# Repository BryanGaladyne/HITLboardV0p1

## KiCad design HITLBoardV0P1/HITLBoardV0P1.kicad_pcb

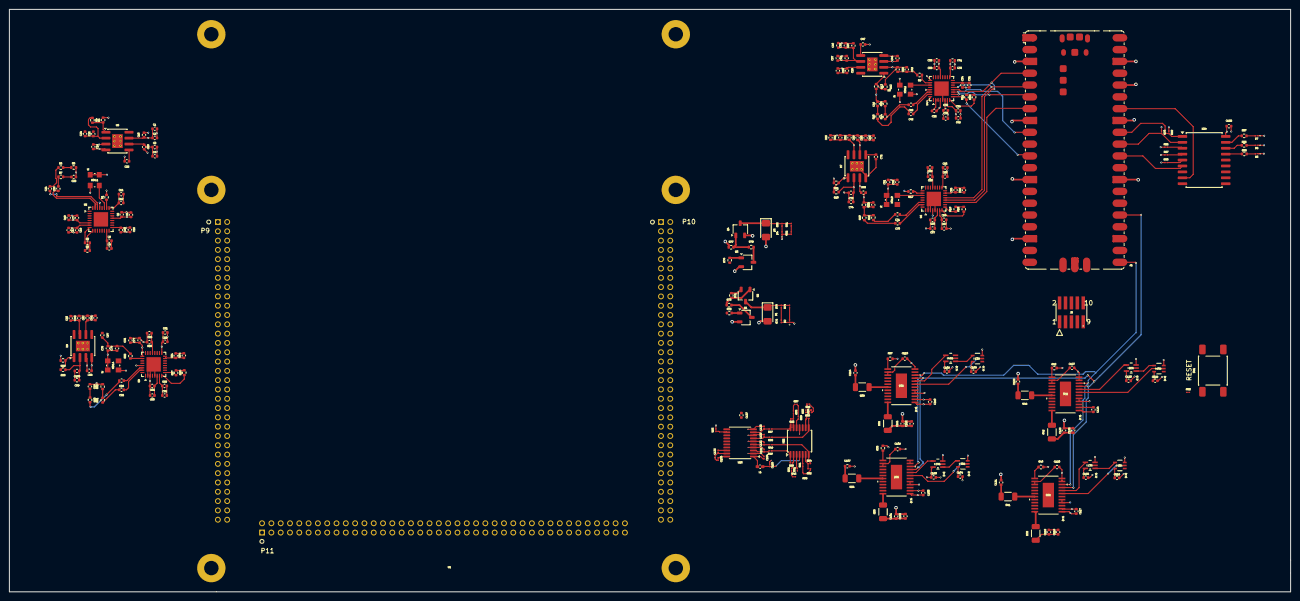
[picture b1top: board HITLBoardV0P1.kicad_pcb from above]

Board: 8 copper layers, 275.4 x 125.2 mm, 267 parts (0 on the bottom side), 160 nets.

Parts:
A1: RaspberryPi_Pico; RaspberryPi_Pico_SMD
C1, C2, C3, C4, C26, C27, C28, C29, C51, C52, C53, C54, C76, C77, C78, C79: 10u; C_0402_1005Metric
C5, C6, C7, C13, C14, C30, C31, C32, C38, C39, C55, C56, C57, C63, C64, C80, C81, C82, C88, C89: 10n; C_0402_1005Metric
C8, C9, C10, C16, C17, C20, C21, C23, C33, C34, C35, C41, C42, C45, C46, C48, C58, C59, C60, C66, C67, C70, C71, C73, C83, C84, C85, C91, C92, C95, C96, C98: .1U; C_0402_1005Metric
C11, C12, C15, C18, C19, C22, C25, C36, C37, C40, C43, C44, C47, C50, C61, C62, C65, C68, C69, C72, C75, C86, C87, C90, C93, C94, C97, C100: 1u; C_0402_1005Metric
C24, C49, C74, C99: 100n; C_0402_1005Metric
C101, C111, C118, C125: 100p; C_0402_1005Metric
C102, C103, C104, C105, C106, C107, C108, C109, C110, C112, C113, C114, C115, C116, C117, C119, C120, C121, C122, C123, C124, C126, C127, C128, C137, C138: 0.1u; C_0402_1005Metric
C129, C131, C132, C133, C134, C136: 0.1u; C_01005_0402Metric
C130, C135: 0.1U; C_01005_0402Metric
D1, D3: D_Schottky; D_1206_3216Metric_Pad1.42x1.75mm_HandSolder
D2, D4, D5, D6, D7: LED; LED_01005_0402Metric
J2: FTSH-105-01-L-DV; CON10_2X5_DU_FTSH_SAI
L1: L_Ferrite; L_0402_1005Metric_Pad0.77x0.64mm_HandSolder
Q1, Q3: NPN; TSOT-23_KSC1623GMTF
Q2, Q4: PMOS; TSOT-23_ZXMP6A14FQ
R1, R9, R17, R25: 12.4K; R_0402_1005Metric
R2, R3, R10, R11, R18, R19, R26, R27, R71, R77: 10K; R_0402_1005Metric
R4, R12, R20, R28: 2.94K; R_0402_1005Metric
R5, R13, R21, R29: 1.13K; R_0402_1005Metric
R6, R7, R14, R15, R22, R23, R30, R31: 49.9K; R_0402_1005Metric
R8, R16, R24, R32: 100K; R_0402_1005Metric
R33, R36, R39, R42: 10; R_1206_3216Metric
R34, R38, R41, R44: 15; R_1206_3216Metric
R35, R37, R40, R43: 15K; R_0402_1005Metric
R45, R46, R57, R58: 150; R_01005_0402Metric
R47, R48, R49, R50, R74, R80: 500; R_01005_0402Metric
R51, R52, R53, R54, R56, R59, R60, R61, R62, R63, R64: 100K; R_01005_0402Metric
R55: 1K; R_01005_0402Metric
R65, R66, R67, R68, R69, R70, R75, R81, R83: 10K; R_01005_0402Metric
R72, R78: 33; R_0402_1005Metric
R73, R79: 4.7K; R_0402_1005Metric
R76, R82: 3500; R_01005_0402Metric
R85, R86, R87: 75; R_0402_1005Metric
SW1: SW_Push; SW_Push_1P1T_NO_E-Switch_TL3301NxxxxxG
U1: TMDX570LC43HDK_Connectors; TMDX570LC43HDK
U2, U4, U6, U8: LAN8650B1-E/LMX; QFN-32-1EP_5x5mm_P0.5mm_EP3.1x3.1mm
U3, U5, U7, U9: LP38852MRX-ADJ/NOPB; SOIC-8-1EP_3.9x4.9mm_P1.27mm_EP2.29x3mm_ThermalVias
U10, U15, U18, U21: DAC7750IPWPR; PWP24_TEX
U11, U13, U16, U19: NC7SZ04P5X; SC-88A-5_1P35X2P2_ONS
U12, U14, U17, U20: SN74LVC1G08DCKR; DCK5
U22: TLV4387PWR; TSSOP-14_4.4x5mm_P0.65mm
U23: ADS131M04QPWRQ1; TSSOP-20_4.4x6.5mm_P0.65mm
U24: MCP23008-E/SO; SOIC-18W_7.5x11.6mm_P1.27mm
XTAL1, XTAL2, XTAL3, XTAL4: ECS-2520S33-250-FN-TR; ECS-2520S_ECS

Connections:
+3.3VP: A1.36 (3V3), C103.1, C104.1, C105.1, C108.1, C109.1, C110.1, C115.1, C116.1, C117.1, C122.1, C123.1, C124.1, C138.1, J2.1, R69.1, R70.1, R83.1, U10.2 (DVDD), U11.5 (VCC), U12.5 (VCC), U13.5 (VCC), U14.5 (VCC), U15.2 (DVDD), U16.5 (VCC), U17.5 (VCC), U18.2 (DVDD), U19.5 (VCC), U20.5 (VCC), U21.2 (DVDD), U24.18 (VDD)
+3V3: C1.1, C2.1, C3.1, C4.1, C11.1, C12.1, C13.1, C14.1, C15.1, C16.1, C17.1, C18.1, C26.1, C27.1, C28.1, C29.1, C36.1, C37.1, C38.1, C39.1, C40.1, C41.1, C42.1, C43.1, C51.1, C52.1, C53.1, C54.1, C61.1, C62.1, C63.1, C64.1, C65.1, C66.1, C67.1, C68.1, C76.1, C77.1, C78.1, C79.1, C86.1, C87.1, C88.1, C89.1, C90.1, C91.1, C92.1, C93.1, C129.1, C136.1, C137.1, L1.1, R2.2, R3.2, R10.2, R11.2, R18.2, R19.2, R26.2, R27.2, R65.2, U2.4 (TEST), U2.7 (VDDP), U2.17 (VDDP), U2.25 (VDDAU), U2.29 (VDDA), U3.6 (EN), U3.7 (IN), U4.4 (TEST), U4.7 (VDDP), U4.17 (VDDP), U4.25 (VDDAU), U4.29 (VDDA), U5.6 (EN), U5.7 (IN), U6.4 (TEST), U6.7 (VDDP), U6.17 (VDDP), U6.25 (VDDAU), U6.29 (VDDA), U7.6 (EN), U7.7 (IN), U8.4 (TEST), U8.7 (VDDP), U8.17 (VDDP), U8.25 (VDDAU), U8.29 (VDDA), U9.6 (EN), U9.7 (IN), U22.4 (V+), U23.20 (DVDD), XTAL1.1 (TRI-STATE), XTAL1.4 (VDD), XTAL2.1 (TRI-STATE), XTAL2.4 (VDD), XTAL3.1 (TRI-STATE), XTAL3.4 (VDD), XTAL4.1 (TRI-STATE), XTAL4.4 (VDD)
+5V: C19.1, C44.1, C69.1, C94.1, U3.3 (BIAS), U5.3 (BIAS), U7.3 (BIAS), U9.3 (BIAS)
+12V: C101.1, C102.1, C111.1, C112.1, C118.1, C119.1, C125.1, C126.1, Q2.3 (S), Q4.3 (S), R33.1, R36.1, R39.1, R42.1, R71.1, R77.1, U1.P9-1 (EXP_12V), U1.P9-3 (EXP_12V), U1.P9-65 (EXP_12V), U1.P10-1 (EXP_12V), U1.P10-65 (EXP_12V), U1.P11-1 (EXP_12V), U1.P11-3 (EXP_12V)
/CurrentInstrument/A_IN_0: C131.1, R48.2, U23.3 (A_IN_0_+)
/CurrentInstrument/A_IN_1: C132.1, R49.2, U23.5 (A_IN_1_+)
/CurrentInstrument/A_IN_2: C133.1, R50.2, U23.7 (A_IN_2_+)
/CurrentInstrument/A_IN_3: C130.1, R47.2, U23.9 (A_IN_3_+)
/CurrentInstrument/Out_A: R48.1, R55.2, U22.1 (OUT_A)
/CurrentInstrument/Out_B: R49.1, R64.2, U22.7 (OUT_B)
/CurrentInstrument/Out_C: R50.1, R56.2, U22.8 (OUT_C)
/CurrentInstrument/Out_D: R47.1, R63.2, U22.14 (OUT_D)
/DAC/AVDD: R33.2, U10.24 (AVDD)
/DAC/IOUT: R34.1, U10.19 (IOUT)
/DAC/ISET_R: R35.1, U10.13 (ISET-R)
/DAC/LATCH_N: U11.4 (A_N=Y), U12.1 (A)
/DAC/REFOUT: C106.1, U10.14 (REFOUT), U10.15 (REFIN)
/DAC/SCLK_AND_LATCH_N: U10.8 (SCLK), U12.4 (Y)
/DAC_CLR0: A1.17 (GPIO13), U10.6 (CLR)
/DAC_CLR1: A1.19 (GPIO14), U15.6 (CLR)
/DAC_CLR2: A1.20 (GPIO15), U18.6 (CLR)
/DAC_CLR3: A1.26 (GPIO20), U21.6 (CLR)
/DAC_LATCH0: A1.12 (GPIO9), U10.7 (LATCH), U11.2 (A)
/DAC_LATCH1: A1.14 (GPIO10), U13.2 (A), U15.7 (LATCH)
/DAC_LATCH2: A1.15 (GPIO11), U16.2 (A), U18.7 (LATCH)
/DAC_LATCH3: A1.16 (GPIO12), U19.2 (A), U21.7 (LATCH)
/ETH_10T1S_A_TRXN: C45.2, R15.1
/ETH_10T1S_A_TRXP: C46.2, R14.1
/ETH_10T1S_B_TRXN: C70.2, C95.2, R23.1, R31.1
/ETH_10T1S_B_TRXP: C71.2, C96.2, R22.1, R30.1
/Ethernet2/1V8: C30.1, C31.1, C32.1, C33.1, C34.1, C35.1, C49.1, C50.1, R12.1, U4.6 (VDDC), U4.15 (VDDC), U4.21 (VDDC), U5.2 (OUT)
/Ethernet2/BIAS: R9.1, U4.26 (RBIAS)
/Ethernet2/TRX_DN: C45.1, U4.31 (TRXN)
/Ethernet2/TRX_DP: C46.1, U4.30 (TRXP)
/Ethernet2/U3_ADJ: R12.2, R13.1, U5.1 (ADJ)
/Ethernet2/U3_SS: C47.1, U5.5 (SS)
/Ethernet2/XTI_U2: U4.27 (XTI), XTAL2.3 (OUTPUT)
/Ethernet/1V8_U2: C5.1, C6.1, C7.1, C8.1, C9.1, C10.1, C24.1, C25.1, R4.1, U2.6 (VDDC), U2.15 (VDDC), U2.21 (VDDC), U3.2 (OUT)
/Ethernet/BIAS: R1.1, U2.26 (RBIAS)
/Ethernet/ETH_10T1S_TRX_DN: C20.2, R7.1
/Ethernet/ETH_10T1S_TRX_DP: C21.2, R6.1
/Ethernet/TRX_DN: C20.1, U2.31 (TRXN)
/Ethernet/TRX_DP: C21.1, U2.30 (TRXP)
/Ethernet/U3_ADJ: R4.2, R5.1, U3.1 (ADJ)
/Ethernet/U3_SS: C22.1, U3.5 (SS)
/Ethernet/XTI_U2: U2.27 (XTI), XTAL1.3 (OUTPUT)
/GPIO_XPNDR_IRQ: A1.34 (GPIO28_ADC2), U24.8 (INT)
/I2C_GPIO_EXPANDER/A0: R68.2, U24.5 (A0)
/I2C_GPIO_EXPANDER/A1: R67.2, U24.4 (A1)
/I2C_GPIO_EXPANDER/A2: R66.2, U24.3 (A2)
/IRQ_N_0: A1.10 (GPIO7), R19.1, U6.9 (IRQ_N)
/IRQ_N_1: A1.11 (GPIO8), R11.1, U4.9 (IRQ_N)
/I_LOOP_1: C107.1, R34.2, R45.2, R51.1
/I_LOOP_2: C114.1, R38.2, R58.2, R61.1
/I_LOOP_3: C121.1, R41.2, R46.2, R53.1
/I_LOOP_4: C128.1, R44.2, R57.2, R59.1
/LAN1_IRQ_N: R3.1, U1.P11-27 (GIOB_1), U2.9 (IRQ_N)
/LAN1_WAKE: U1.P11-19 (GIOA_1), U2.32 (WAKE_IN)
/LAN2_IRQ_N: R27.1, U1.P11-29 (GIOB_3), U8.9 (IRQ_N)
/LAN2_WAKE: U1.P11-21 (GIOA_3), U8.32 (WAKE_IN)
/LAN_WAKE_0: U6.32 (WAKE_IN), U24.11 (GP1)
/LAN_WAKE_1: U4.32 (WAKE_IN), U24.12 (GP2)
/LED0: R85.1, U24.15 (GP5)
/LED1: R86.1, U24.16 (GP6)
/LED2: R87.1, U24.17 (GP7)
/RESET_N: A1.30 (RUN), J2.10, R2.1, R10.1, R18.1, R26.1, R83.2, SW1.1, U1.P9-60 (POR_RST_N), U2.8 (RESET_N), U4.8 (RESET_N), U6.8 (RESET_N), U8.8 (RESET_N), U24.6 (*RESET)
/RPI_I2C_SCL: A1.32 (GPIO27_ADC1), R69.2, U24.1 (SCL)
/RPI_I2C_SDA: A1.31 (GPIO26_ADC0), R70.2, U24.2 (SDA)
/RPI_SPI0_MISO: A1.6 (GPIO4), U4.10 (SDO), U6.10 (SDO)
/RPI_SPI0_MOSI: A1.5 (GPIO3), U4.13 (SDI), U6.13 (SDI)
/RPI_SPI0_SCK: A1.4 (GPIO2), U4.12 (SCLK), U6.12 (SCLK)
/RPI_SPI1_MISO: A1.21 (GPIO16), U10.10 (SDO), U15.10 (SDO), U18.10 (SDO), U21.10 (SDO)
/RPI_SPI1_MOSI: A1.25 (GPIO19), U10.9 (DIN), U15.9 (DIN), U18.9 (DIN), U21.9 (DIN)
/RPI_SPI1_SCK: A1.24 (GPIO18), U12.2 (B), U17.2 (B), U20.2 (B)
/RPI_UART1_RX: A1.29 (GPIO22), U1.P11-6 (LIN_TX)
/RPI_UART1_TX: A1.27 (GPIO21), U1.P11-5 (LIN_RX)
/RaspberryPiPico/SWCLK: A1.D1 (SWCLK), J2.4
/RaspberryPiPico/SWDIO: A1.D3 (SWDIO), J2.2
/SPI0_CS0: A1.7 (GPIO5), U6.11 (CS_N)
/SPI0_CS1: A1.9 (GPIO6), U4.11 (CS_N)
/SV_EN_1: R72.1, U1.P11-31 (GIOB_5)
/SV_EN_2: R78.1, U1.P11-33 (GIOB_7)
/SV_ON_1: R75.1, R76.2, U24.13 (GP3)
/SV_ON_2: R81.1, R82.2, U24.14 (GP4)
/Solenoid-Valve1/SV_24VDC_OUT: D3.1 (K), Q4.1 (D), R80.2, R81.2
/Solenoid-Valve/SV_24VDC_OUT: D1.1 (K), Q2.1 (D), R74.2, R75.2
/TMDX_SPI1_CS0_N: U1.P9-8 (SPI1_CS0_N), U2.11 (CS_N)
/TMDX_SPI1_SCLK: U1.P9-6 (SPI1_CLK), U2.12 (SCLK)
/TMDX_SPI1_SIMO: U1.P9-11 (SPI1_SIMO), U2.13 (SDI)
/TMDX_SPI1_SOMI: U1.P9-12 (SPI1_SOMI), U2.10 (SDO)
/TMDX_SPI3_CS1_N: R65.1, U1.P11-75 (SPI3_CS1_NHET125), U23.12 (CHIP_SELECT_N)
/TMDX_SPI3_SCLK: U1.P11-78 (SPI3_CLK), U23.14 (SCLK)
/TMDX_SPI3_SIMO: U1.P11-73 (SPI3_SIMO), U23.16 (DIN)
/TMDX_SPI3_SOMI: U1.P11-74 (SPI3_SOMI), U23.15 (DOUT)
/TMDX_SPI5_CS0_N: U1.P9-18 (SPI5_CS0_N), U8.11 (CS_N)
/TMDX_SPI5_SCLK: U1.P9-16 (SPI5_CLK), U8.12 (SCLK)
/TMDX_SPI5_SIMO: U1.P9-21 (SPI5_SIMO_0), U8.13 (SDI)
/TMDX_SPI5_SOMI: U1.P9-22 (SPI5_SOMI_0), U8.10 (SDO)
/dac2/AVDD: R36.2, U15.24 (AVDD)
/dac2/IOUT: R38.1, U15.19 (IOUT)
/dac2/ISET_R: R37.1, U15.13 (ISET-R)
/dac2/LATCH_N: U13.4 (A_N=Y), U14.1 (A)
/dac2/REFOUT: C113.1, U15.14 (REFOUT), U15.15 (REFIN)
/dac2/SCLK_AND_LATCH_N: U14.4 (Y), U15.8 (SCLK)
/dac3/AVDD: R39.2, U18.24 (AVDD)
/dac3/IOUT: R41.1, U18.19 (IOUT)
/dac3/ISET_R: R40.1, U18.13 (ISET-R)
/dac3/LATCH_N: U16.4 (A_N=Y), U17.1 (A)
/dac3/REFOUT: C120.1, U18.14 (REFOUT), U18.15 (REFIN)
/dac3/SCLK_AND_LATCH_N: U17.4 (Y), U18.8 (SCLK)
/dac4/AVDD: R42.2, U21.24 (AVDD)
/dac4/IOUT: R44.1, U21.19 (IOUT)
/dac4/ISET_R: R43.1, U21.13 (ISET-R)
/dac4/LATCH_N: U19.4 (A_N=Y), U20.1 (A)
/dac4/REFOUT: C127.1, U21.14 (REFOUT), U21.15 (REFIN)
/dac4/SCLK_AND_LATCH_N: U20.4 (Y), U21.8 (SCLK)
/ethernet3/1V8: C55.1, C56.1, C57.1, C58.1, C59.1, C60.1, C74.1, C75.1, R20.1, U6.6 (VDDC), U6.15 (VDDC), U6.21 (VDDC), U7.2 (OUT)
/ethernet3/BIAS: R17.1, U6.26 (RBIAS)
/ethernet3/TRX_DN: C70.1, U6.31 (TRXN)
/ethernet3/TRX_DP: C71.1, U6.30 (TRXP)
/ethernet3/U3_ADJ: R20.2, R21.1, U7.1 (ADJ)
/ethernet3/U3_SS: C72.1, U7.5 (SS)
/ethernet3/XTI_U2: U6.27 (XTI), XTAL3.3 (OUTPUT)
/ethernet4/1V8: C80.1, C81.1, C82.1, C83.1, C84.1, C85.1, C99.1, C100.1, R28.1, U8.6 (VDDC), U8.15 (VDDC), U8.21 (VDDC), U9.2 (OUT)
/ethernet4/BIAS: R25.1, U8.26 (RBIAS)
/ethernet4/TRX_DN: C95.1, U8.31 (TRXN)
/ethernet4/TRX_DP: C96.1, U8.30 (TRXP)
/ethernet4/U3_ADJ: R28.2, R29.1, U9.1 (ADJ)
/ethernet4/U3_SS: C97.1, U9.5 (SS)
/ethernet4/XTI_U2: U8.27 (XTI), XTAL4.3 (OUTPUT)
GND: A1.3 (GND), A1.8 (GND), A1.13 (GND), A1.18 (GND), A1.23 (GND), A1.28 (GND), A1.33 (AGND), A1.38 (GND), A1.D2 (GND), A1.TP1 (USB_GND), C1.2, C2.2, C3.2, C4.2, C5.2, C6.2, C7.2, C8.2, C9.2, C10.2, C11.2, C12.2, C13.2, C14.2, C15.2, C16.2, C17.2, C18.2, C19.2, C22.2, C23.1, C24.2, C25.2, C26.2, C27.2, C28.2, C29.2, C30.2, C31.2, C32.2, C33.2, C34.2, C35.2, C36.2, C37.2, C38.2, C39.2, C40.2, C41.2, C42.2, C43.2, C44.2, C47.2, C48.1, C49.2, C50.2, C51.2, C52.2, C53.2, C54.2, C55.2, C56.2, C57.2, C58.2, C59.2, C60.2, C61.2, C62.2, C63.2, C64.2, C65.2, C66.2, C67.2, C68.2, C69.2, C72.2, C73.1, C74.2, C75.2, C76.2, C77.2, C78.2, C79.2, C80.2, C81.2, C82.2, C83.2, C84.2, C85.2, C86.2, C87.2, C88.2, C89.2, C90.2, C91.2, C92.2, C93.2, C94.2, C97.2, C98.1, C99.2, C100.2, C101.2, C102.2, C103.2, C104.2, C105.2, C106.2, C107.2, C108.2, C109.2, C110.2, C111.2, C112.2, C113.2, C114.2, C115.2, C116.2, C117.2, C118.2, C119.2, C120.2, C121.2, C122.2, C123.2, C124.2, C125.2, C126.2, C127.2, C128.2, C129.2, C130.2, C131.2, C132.2, C133.2, C134.2, C135.1, C136.2, C137.2, C138.2, D1.2 (A), D2.1 (K), D3.2 (A), D4.1 (K), D5.1 (K), D6.1 (K), D7.1 (K), J2.3, J2.5, J2.9, Q1.3 (E), Q3.3 (E), R1.2, R5.2, R8.2, R9.2, R13.2, R16.2, R17.2, R21.2, R24.2, R25.2, R29.2, R32.2, R35.2, R37.2, R40.2, R43.2, R66.1, R67.1, R68.1, R76.1, R82.1, SW1.2, U1.P9-2 (GND), U1.P9-4 (GND), U1.P9-13 (GND), U1.P9-14 (GND), U1.P9-29 (GND), U1.P9-30 (GND), U1.P9-39 (GND), U1.P9-40 (GND), U1.P9-49 (GND), U1.P9-50 (GND), U1.P9-59 (GND), U1.P9-66 (GND), U1.P10-29 (GND), U1.P10-30 (GND), U1.P10-39 (GND), U1.P10-40 (GND), U1.P10-57 (GND), U1.P10-58 (GND), U1.P10-66 (GND), U2.2 (VSS), U2.3 (VSS), U2.5 (VSS), U2.33 (VSS), U3.4 (GND), U4.2 (VSS), U4.3 (VSS), U4.5 (VSS), U4.33 (VSS), U5.4 (GND), U6.2 (VSS), U6.3 (VSS), U6.5 (VSS), U6.33 (VSS), U7.4 (GND), U7.9 (DAP), U8.2 (VSS), U8.3 (VSS), U8.5 (VSS), U8.33 (VSS), U9.4 (GND), U9.9 (DAP), U10.1 (GND), U10.4 (GND), U10.5 (GND), U10.11 (GND), U10.12 (GND), U11.3 (GND), U12.3 (GND), U13.3 (GND), U14.3 (GND), U15.1 (GND), U15.4 (GND), U15.5 (GND), U15.11 (GND), U15.12 (GND), U16.3 (GND), U17.3 (GND), U18.1 (GND), U18.4 (GND), U18.5 (GND), U18.11 (GND), U18.12 (GND), U19.3 (GND), U20.3 (GND), U21.1 (GND), U21.4 (GND), U21.5 (GND), U21.11 (GND), U21.12 (GND), U22.11 (V-), U23.2 (AGND), U23.4 (A_IN_0_-), U23.6 (A_IN_1_-), U23.8 (A_IN_2_-), U23.10 (A_IN_3_-), U23.19 (DGND), U24.9 (VSS), XTAL1.2 (GND), XTAL2.2 (GND), XTAL3.2 (GND), XTAL4.2 (GND)
unnamed: C23.2, R6.2, R7.2, R8.1
unnamed: C48.2, R14.2, R15.2, R16.1
unnamed: C73.2, R22.2, R23.2, R24.1
unnamed: C98.2, R30.2, R31.2, R32.1
unnamed: D2.2 (A), R74.1
unnamed: D4.2 (A), R80.1
unnamed: D5.2 (A), R85.2
unnamed: D6.2 (A), R86.2
unnamed: D7.2 (A), R87.2
unnamed: Q1.2 (B), R72.2
unnamed: Q1.1 (C), R73.2
unnamed: Q2.2 (G), R71.2, R73.1
unnamed: Q3.2 (B), R78.2
unnamed: Q3.1 (C), R79.2
unnamed: Q4.2 (G), R77.2, R79.1
unnamed: R45.1, R52.1
unnamed: R46.1, R54.1
unnamed: R57.1, R60.1
unnamed: R58.1, R62.1
unnamed: R51.2, U22.3 (IN_A_+)
unnamed: R52.2, R55.1, U22.2 (IN_A_-)
unnamed: R61.2, U22.5 (IN_B_+)
unnamed: R62.2, R64.1, U22.6 (IN_B_-)
unnamed: R53.2, U22.10 (IN_C_+)
unnamed: R54.2, R56.1, U22.9 (IN_C_-)
unnamed: R59.2, U22.12 (IN_D_+)
unnamed: R60.2, R63.1, U22.13 (IN_D_-)
unnamed: C134.1, L1.2, U23.1 (AVDD)
unnamed: C135.2, U23.18 (CAP)

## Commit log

2026-04-15 IN PROGRESS
2026-04-15 complete ethernet schematic capture
2026-04-16 UPDATE -- IN PROGRESS
2026-04-17 in progress, brute forced lan8650 layouts :( damn you kicad
2026-04-17 UPDATE IN PROGRESS, 4 DACS ADDED AND INITIAL ROUTED IN PCB
2026-04-17 readd pcb layout file after getting kicked in the balls.
2026-04-17 update to board with spi buses assigned
2026-04-17 ADD GPIO EXPANDER FOR RPI PICO
2026-04-17 UPDATE MINOR CHANGES
2026-04-17 ADD SOLENOID VALVE CIRCUIT
2026-04-17 update solenoid valve circuits
2026-04-20 add debug LEDs and reset_n button for system reset
2026-04-21 add reset button groups
2026-04-21 MINOR UPDATES -- SWTICH ONE LAN TO SPI 5 INSTEAD OF SPI1 ON THE TMDX, SET UP LAN8650S for actual differential pair routing by changing suffix to "_DN" and "_DP" instead of "_N" or "_P" or just "N", "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
2026-04-21 FIX spi 3 on tmdx for current loop ADC, add gpio pin for data ready
2026-04-21 basic organization into layout
2026-04-21 fix ethernet channel that was fubar, beginning layout
2026-04-21 layout in progress
